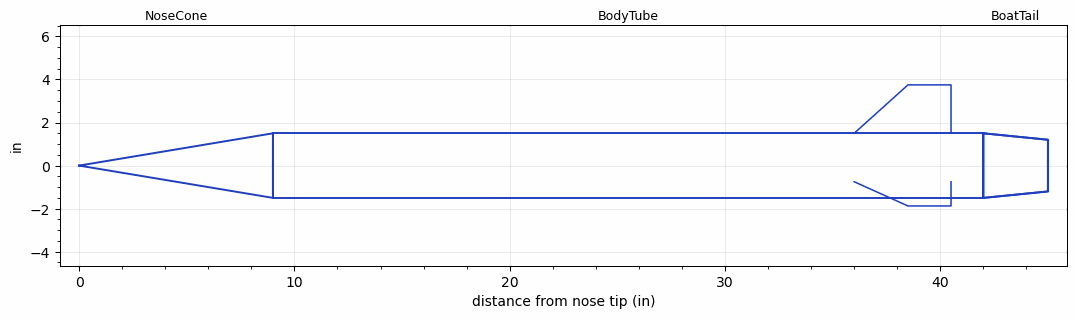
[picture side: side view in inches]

<RASAeroDocument>
 <FileVersion>2</FileVersion>
 <RocketDesign>
  <NoseCone>
   <Length>9</Length>
   <Diameter>3</Diameter>
   <Shape>Conical</Shape>
   <Location>0</Location>
  </NoseCone>
  <BodyTube>
   <Length>33</Length>
   <Diameter>3</Diameter>
   <Location>9</Location>
   <BoattailLength>3</BoattailLength>
   <BoattailRearDiameter>2.4</BoattailRearDiameter>
   <Fin>
    <Count>3</Count>
    <Chord>4.5</Chord>
    <Span>2.25</Span>
    <SweepDistance>2.5</SweepDistance>
    <TipChord>2</TipChord>
    <Thickness>0.125</Thickness>
    <Location>6</Location>
    <AirfoilSection>Square</AirfoilSection>
   </Fin>
  </BodyTube>
  <BoatTail>
   <Length>3</Length>
   <Diameter>3</Diameter>
   <RearDiameter>2.4</RearDiameter>
   <Location>42</Location>
  </BoatTail>
  <Surface>Smooth (Zero Roughness)</Surface>
  <ModifiedBarrowman>False</ModifiedBarrowman>
  <Turbulence>True</Turbulence>
  <UseBooster1>False</UseBooster1>
  <UseBooster2>False</UseBooster2>
  <Comments>Afterbody component study B-finned-boattail</Comments>
 </RocketDesign>
 <LaunchSite>
  <Altitude>0</Altitude>
  <Pressure>29.9214</Pressure>
  <RodAngle>0</RodAngle>
  <RodLength>6.5617</RodLength>
  <Temperature>59</Temperature>
  <WindSpeed>0</WindSpeed>
 </LaunchSite>
 <Recovery>
  <Altitude1>656.168</Altitude1>
  <Altitude2>0</Altitude2>
  <DeviceType1>Parachute</DeviceType1>
  <DeviceType2>None</DeviceType2>
  <Event1>True</Event1>
  <Event2>False</Event2>
  <Size1>24</Size1>
  <Size2>0</Size2>
  <EventType1>Apogee</EventType1>
  <EventType2>None</EventType2>
  <CD1>0.8</CD1>
  <CD2>0</CD2>
 </Recovery>
</RASAeroDocument>
